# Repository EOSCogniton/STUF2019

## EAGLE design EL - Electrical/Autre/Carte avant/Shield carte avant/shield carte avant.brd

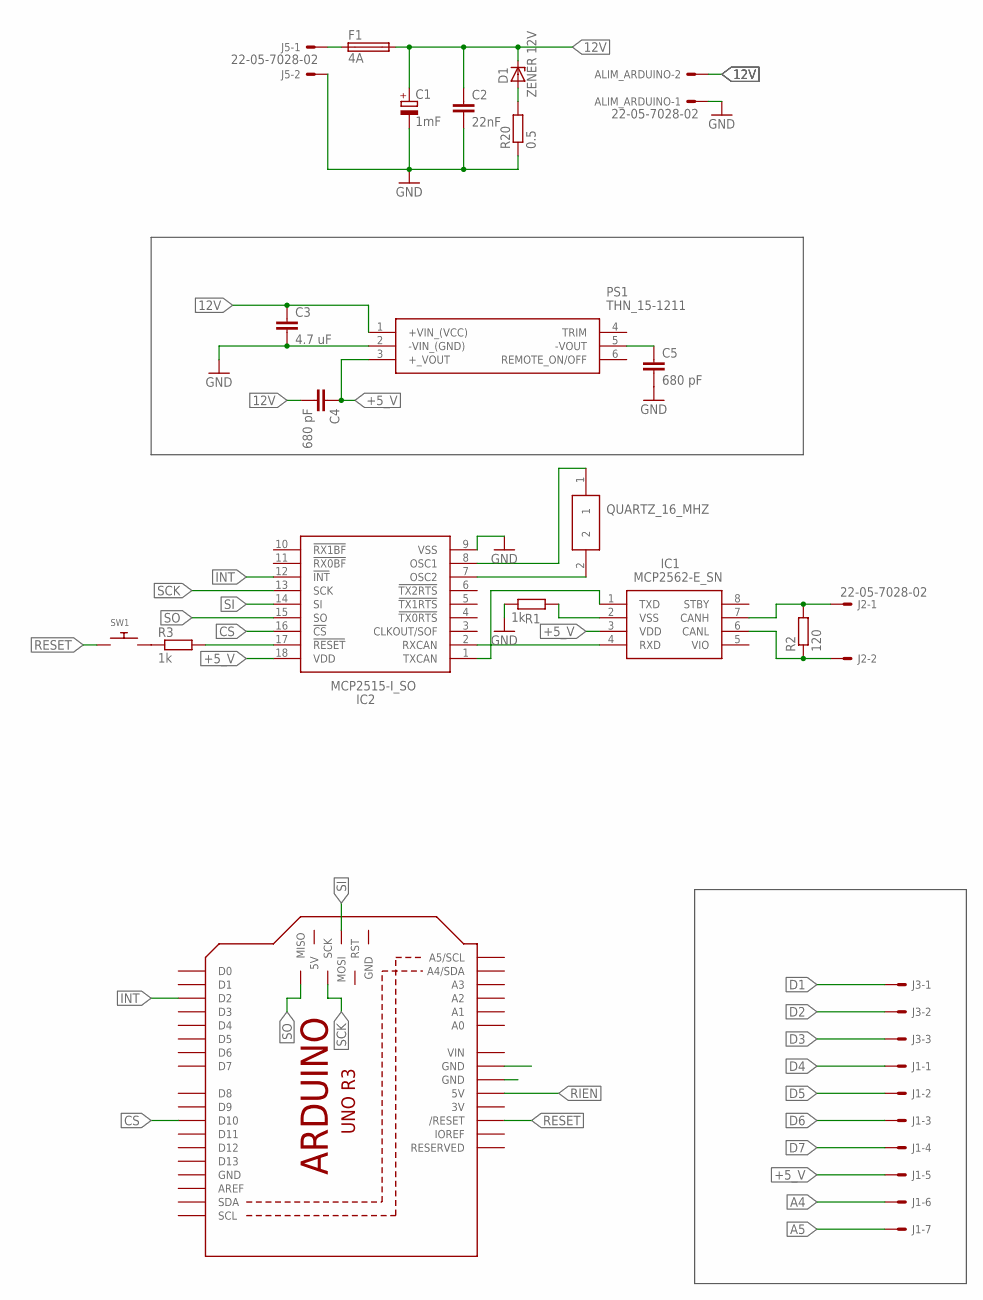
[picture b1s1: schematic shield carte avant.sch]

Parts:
ALIM_ARDUINO: 22-05-7028-02; 7395-02
C1: 1mF; E7,5-16
C2: 22nF; C025-025X050
C3: 4.7 uF; C025-024X044
C4, C5: 680 pF; C025-024X044
D1: ZENER 12V; DO41Z10
F1: 4A; SH25
IC1: MCP2562-E_SN; SOIC127P600X175-8N
IC2: MCP2515-I_SO; SOIC127P1030X265-18N
J1: 22-05-7078-07; 7395-07
J2, J5: 22-05-7028-02; 7395-02
J3: 22-05-7038-03; 7395-03
M1: ARDUINO_R3_ICSP; ARDUINOR3_ICSP
PS1: THN_15-1211; THN-15-SERIES
QUARTZ_16_MHZ: FOXSLF_160-20; HC49SLF_1
R1, R3: 1k; 0204/7
R2: 120; 0204/7
R20: 0.5; 0309/12
SW1: SWITCH_PUSHBUTTONEVQ-PE; TACT_PANA-EVQ

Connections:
3V: M1.3V
12V: ALIM_ARDUINO.2, C1.+, C2.1, C3.1, C4.2, D1.C, F1.2, PS1.1 (+VIN_(VCC))
+5_V: C4.1, IC1.3 (VDD), IC2.18 (VDD), J1.5, PS1.3 (+_VOUT)
A4: J1.6
A5: J1.7
CS: IC2.16 (!CS), M1.D10
D1: J3.1
D2: J3.2
D3: J3.3
D4: J1.1
D5: J1.2
D6: J1.3
D7: J1.4
GND: ALIM_ARDUINO.1, C1.-, C2.2, C3.2, C5.2, IC2.9 (VSS), J5.2, M1.GND, PS1.2 (-VIN_(GND)), R1.1, R20.1
INT: IC2.12 (!INT), M1.D2
unnamed: F1.1, J5.1
unnamed: C5.1, PS1.5 (-VOUT)
unnamed: D1.A, R20.2
unnamed: IC1.1 (TXD), IC2.1 (TXCAN)
unnamed: IC1.4 (RXD), IC2.2 (RXCAN)
unnamed: IC1.2 (VSS), R1.2
unnamed: IC1.7 (CANH), J2.1, R2.2
unnamed: IC1.6 (CANL), J2.2, R2.1
unnamed: IC2.7 (OSC2), QUARTZ_16_MHZ.2
unnamed: IC2.8 (OSC1), QUARTZ_16_MHZ.1
unnamed: R3.1, SW1.P$2
unnamed: IC2.17 (!RESET), R3.2
RESET: M1.RESET (/RESET), SW1.P$1
RIEN: M1.5V
SCK: IC2.13 (SCK), M1.SCK
SI: IC2.14 (SI), M1.MOSI
SO: IC2.15 (SO), M1.MISO
VIN: M1.VIN

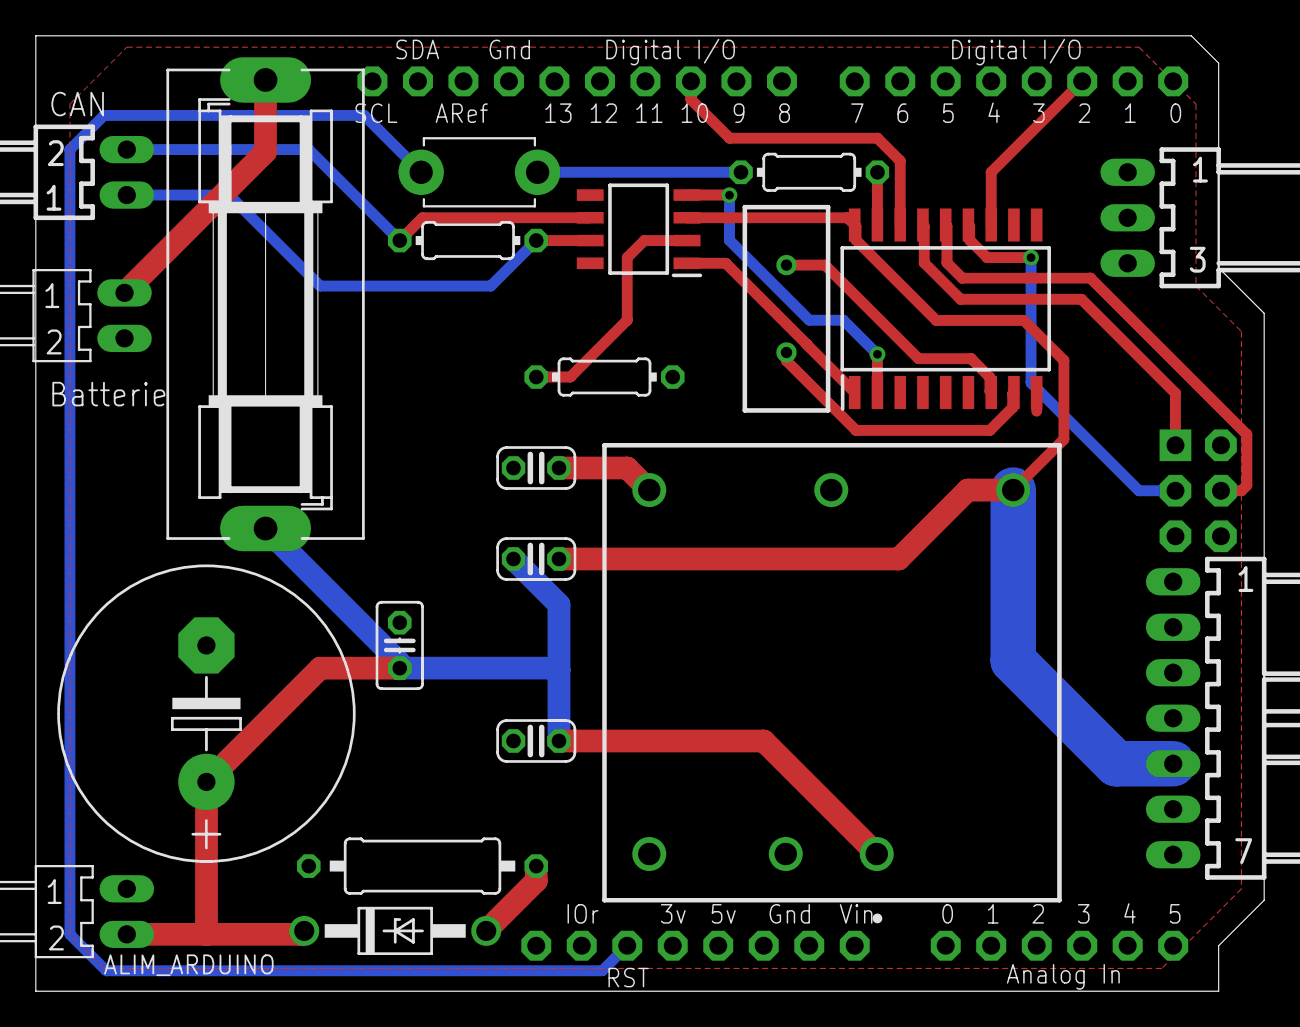
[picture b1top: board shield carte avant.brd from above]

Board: 2 copper layers, 68.6 x 53.3 mm, 22 parts (0 on the bottom side), 21 nets.

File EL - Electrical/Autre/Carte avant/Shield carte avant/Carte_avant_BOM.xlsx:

Qty | Value | Device | Description | Dispo au garage ? | Référence RS |  |  |  | oui
1 |  | SWITCH_PUSHBUTTONEVQ-PE | Buttons | Je sais pas |  |  |  |  | non
1 | 0.5 | R-EU_0309/12 | RESISTOR, European symbol | oui |  |  |  |  | Je sais pas
1 | 120 | R-EU_0204/7 | RESISTOR, European symbol | oui
2 | 1k | R-EU_0204/7 | RESISTOR, European symbol | oui
1 | 1mF | CPOL-EUE7.5-16 | POLARIZED CAPACITOR, European symbol | Je sais pas
2 |  | 22-05-7028-02 | CONNECTOR | oui
1 |  | 22-05-7028-02 | CONNECTOR | oui
1 |  | 22-05-7038-03 | CONNECTOR | Je sais pas
1 |  | 22-05-7078-07 | CONNECTOR | Je sais pas
1 | 22nF | C-EU025-025X050 | CAPACITOR, European symbol | Je sais pas
1 | 4.7 uF | C-EU025-024X044 | CAPACITOR, European symbol | Je sais pas
1 | 4A | SH25 | FUSE HOLDER grid 25 mm, OGN0031 8211, Schurter (Buerklin) | oui
2 | 680 pF | C-EU025-024X044 | CAPACITOR, European symbol | Je sais pas
1 |  | FOXSLF_160-20 | Crystal 16.000MHz HC49S HC-49-SLF Crystal 16MHz, ??30ppm, 2-Pin | Je sais pas
1 |  | MCP2515-I_SO | CAN Controller SPI data filtering SO18 | non
1 |  | MCP2562-E_SN | CAN Transceiver 1Mbps 5V 125degC SOIC8 CAN Transceiver 1MBps IEC 61000-4-2 Stan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 | non
1 |  | THN_15-1211 | TRACOPOWER Isolated DC-DC Converter, Vin 9 18 V dc, Vout 5V dc, I/O isolation 1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 | Je sais pas
1 | ZENER 12V | ZENER-DIODEDO41Z10 | Z-Diode | Je sais pas

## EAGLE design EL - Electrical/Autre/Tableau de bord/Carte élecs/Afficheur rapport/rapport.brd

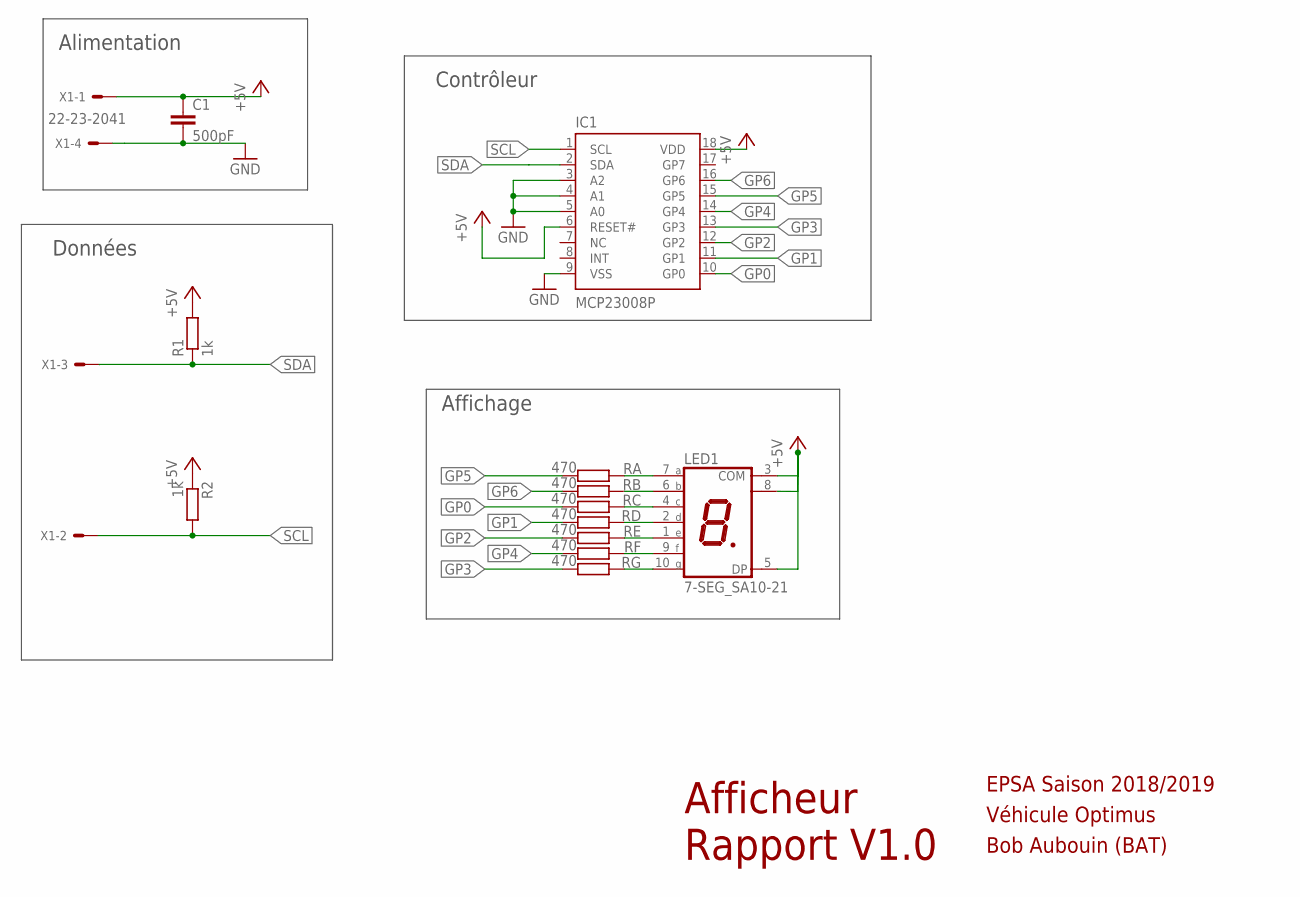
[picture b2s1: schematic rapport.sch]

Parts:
C1: 500pF; C025-025X050
IC1: MCP23008P; DIL18
LED1: 7-SEG_SA10-21; SA10-21
R1, R2: 1k; 0204/7
RA: 470; 0204/7
RB: 470; 0204/7
RC: 470; 0204/7
RD: 470; 0204/7
RE: 470; 0204/7
RF: 470; 0204/7
RG: 470; 0204/7
X1: 22-23-2041

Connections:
+5V: C1.1, IC1.6 (RESET#), IC1.18 (VDD), LED1.3 (COM), LED1.5 (DP), LED1.8 (COM), R1.2, R2.1, X1.1
GND: C1.2, IC1.3 (A2), IC1.4 (A1), IC1.5 (A0), IC1.9 (VSS), X1.4
GP0: IC1.10 (GP0), RC.2
GP1: IC1.11 (GP1), RD.2
GP2: IC1.12 (GP2), RE.2
GP3: IC1.13 (GP3), RG.2
GP4: IC1.14 (GP4), RF.2
GP5: IC1.15 (GP5), RA.2
GP6: IC1.16 (GP6), RB.2
unnamed: LED1.10 (G), RG.1
unnamed: LED1.9 (F), RF.1
unnamed: LED1.1 (E), RE.1
unnamed: LED1.2 (D), RD.1
unnamed: LED1.4 (C), RC.1
unnamed: LED1.6 (B), RB.1
unnamed: LED1.7 (A), RA.1
SCL: IC1.1 (SCL), R2.2, X1.2
SDA: IC1.2 (SDA), R1.1, X1.3

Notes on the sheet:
Afficheur Rapport V1.0
EPSA Saison 2018/2019
Alimentation
Contrôleur
Données
Affichage
Véhicule Optimus
Bob Aubouin (BAT)

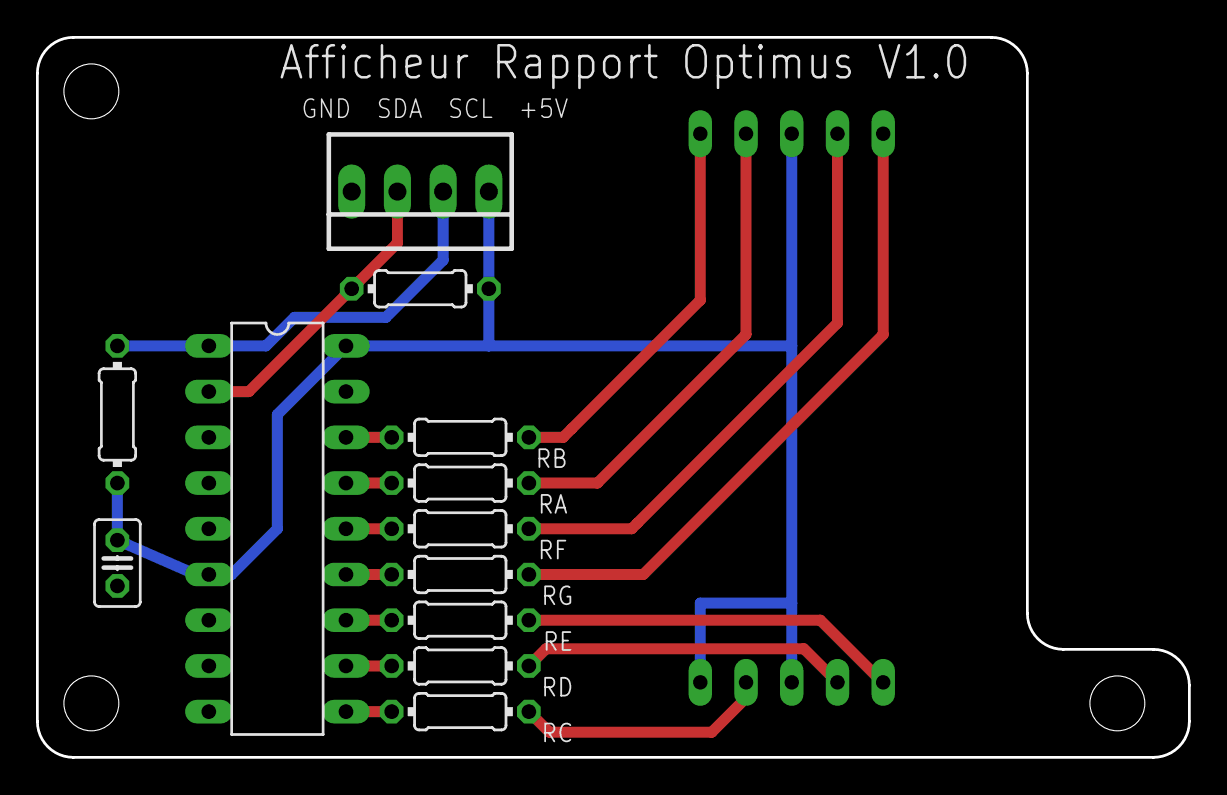
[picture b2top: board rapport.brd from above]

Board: 2 copper layers, 64.0 x 40.0 mm, 13 parts (1 on the bottom side), 18 nets.

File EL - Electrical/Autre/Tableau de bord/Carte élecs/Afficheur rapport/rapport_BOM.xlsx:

Qty | Value | Device | Description | Dispo au garage ? | Référence RS |  |  |  |  |  | oui
2 | 1k | R-EU_0204/7 | RESISTOR, European symbol | oui |  |  |  |  |  |  | non
1 |  | 22-23-2041 | .100 (2.54mm) Center Header - 4 Pin" | Je sais pas | 679-5596 |  |  |  |  |  | Je sais pas
7 | 470 | R-EU_0204/7 | RESISTOR, European symbol | oui
1 | 500pF | C-EU025-025X050 | CAPACITOR, European symbol | Je sais pas | 831-3026
1 |  | 7-SEG_SA10-21 | Kingbright 14.2mm (0.56 INCH) SINGLE DIGIT NUMERIC DUISPLAY | oui
1 |  | MCP23008P | 8-Bit I/O Expander with I2C Interface | oui

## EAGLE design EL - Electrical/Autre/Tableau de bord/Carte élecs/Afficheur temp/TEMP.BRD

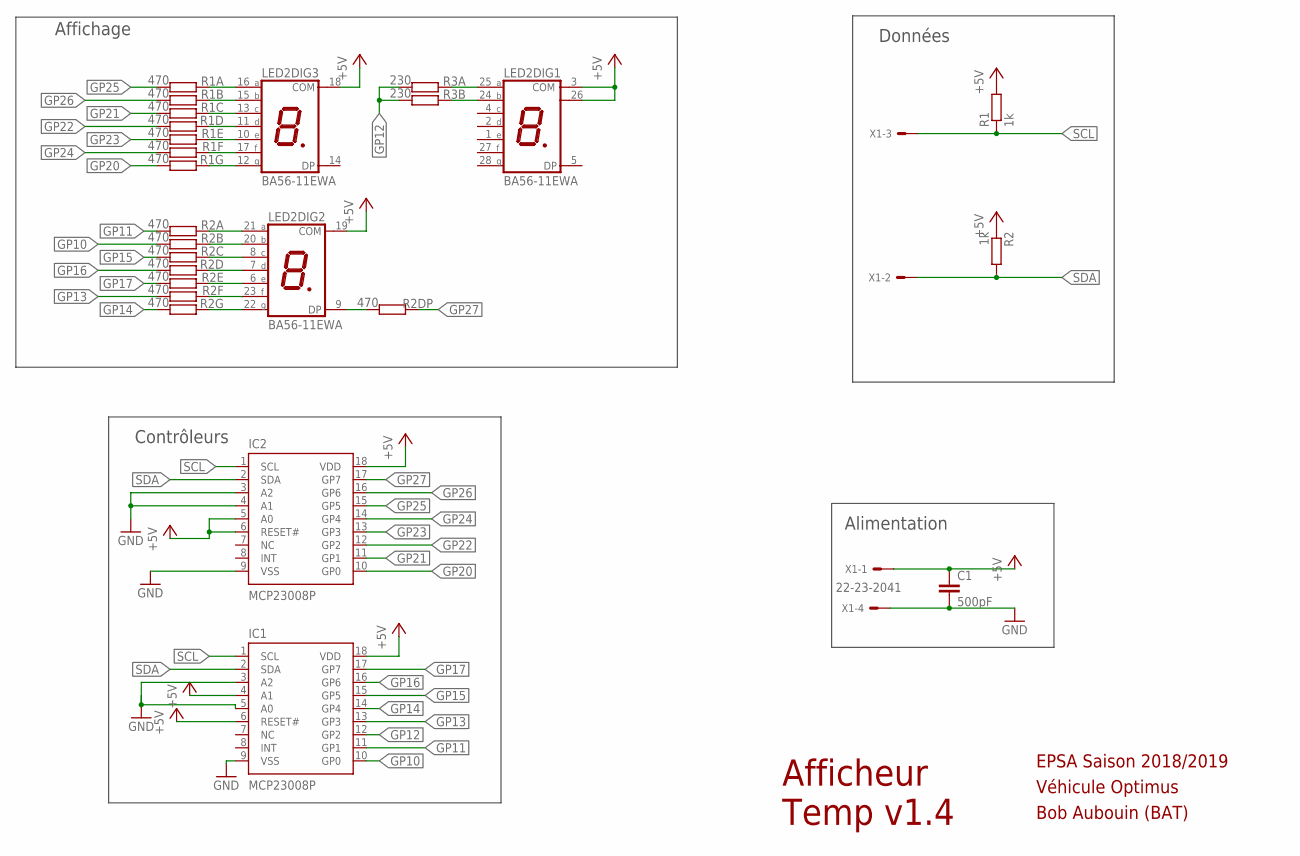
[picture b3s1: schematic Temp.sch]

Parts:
C1: 500pF; C025-025X050
IC1, IC2: MCP23008P; DIL18
LED2: BA56-11EWA; BA/BC56
R1, R2: 1k; 0204/7
R1A, R1B, R1C, R1D, R1E, R1F, R1G, R2A, R2B, R2C, R2D, R2DP, R2E, R2F, R2G: 470; 0204/7
R3A, R3B: 230; 0204/7
X1: 22-23-2041

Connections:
+5V: C1.1, IC1.4 (A1), IC1.6 (RESET#), IC1.18 (VDD), IC2.5 (A0), IC2.6 (RESET#), IC2.18 (VDD), LED2.3 (COM), LED2.18 (COM), LED2.19 (COM), LED2.26 (COM), R1.2, R2.1, X1.1
GND: C1.2, IC1.3 (A2), IC1.5 (A0), IC1.9 (VSS), IC2.3 (A2), IC2.4 (A1), IC2.9 (VSS), X1.4
GP10: IC1.10 (GP0), R2B.2
GP11: IC1.11 (GP1), R2A.2
GP12: IC1.12 (GP2), R3A.2, R3B.2
GP13: IC1.13 (GP3), R2F.2
GP14: IC1.14 (GP4), R2G.2
GP15: IC1.15 (GP5), R2C.2
GP16: IC1.16 (GP6), R2D.2
GP17: IC1.17 (GP7), R2E.2
GP20: IC2.10 (GP0), R1G.2
GP21: IC2.11 (GP1), R1C.2
GP22: IC2.12 (GP2), R1D.2
GP23: IC2.13 (GP3), R1E.2
GP24: IC2.14 (GP4), R1F.2
GP25: IC2.15 (GP5), R1A.2
GP26: IC2.16 (GP6), R1B.2
GP27: IC2.17 (GP7), R2DP.1
unnamed: LED2.16 (A), R1A.1
unnamed: LED2.15 (B), R1B.1
unnamed: LED2.13 (C), R1C.1
unnamed: LED2.11 (D), R1D.1
unnamed: LED2.10 (E), R1E.1
unnamed: LED2.17 (F), R1F.1
unnamed: LED2.12 (G), R1G.1
unnamed: LED2.21 (A), R2A.1
unnamed: LED2.20 (B), R2B.1
unnamed: LED2.8 (C), R2C.1
unnamed: LED2.7 (D), R2D.1
unnamed: LED2.6 (E), R2E.1
unnamed: LED2.23 (F), R2F.1
unnamed: LED2.22 (G), R2G.1
unnamed: LED2.9 (DP), R2DP.2
unnamed: LED2.24 (B), R3B.1
unnamed: LED2.25 (A), R3A.1
SCL: IC1.1 (SCL), IC2.1 (SCL), R1.1, X1.3
SDA: IC1.2 (SDA), IC2.2 (SDA), R2.2, X1.2

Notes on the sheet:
Afficheur Temp v1.4
EPSA Saison 2018/2019
Alimentation
Contrôleurs
Données
Affichage
Véhicule Optimus
Bob Aubouin (BAT)

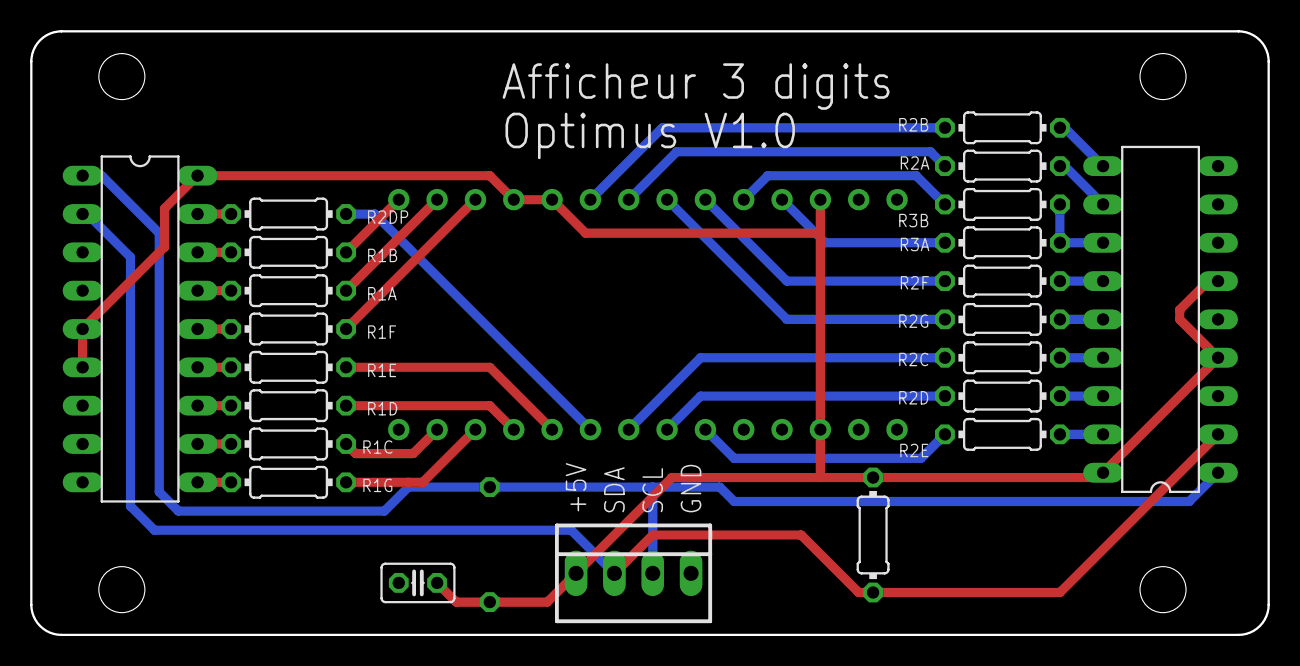
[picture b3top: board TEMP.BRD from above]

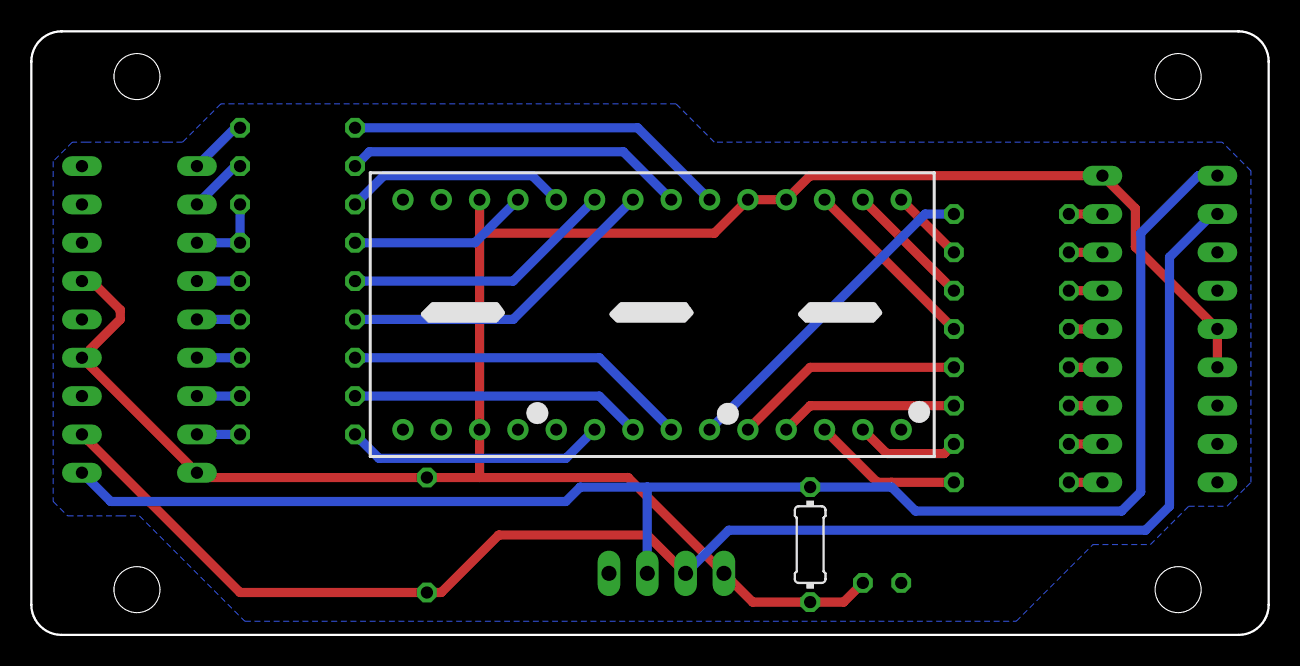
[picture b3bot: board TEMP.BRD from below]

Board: 2 copper layers, 82.0 x 40.0 mm, 24 parts (2 on the bottom side), 37 nets.

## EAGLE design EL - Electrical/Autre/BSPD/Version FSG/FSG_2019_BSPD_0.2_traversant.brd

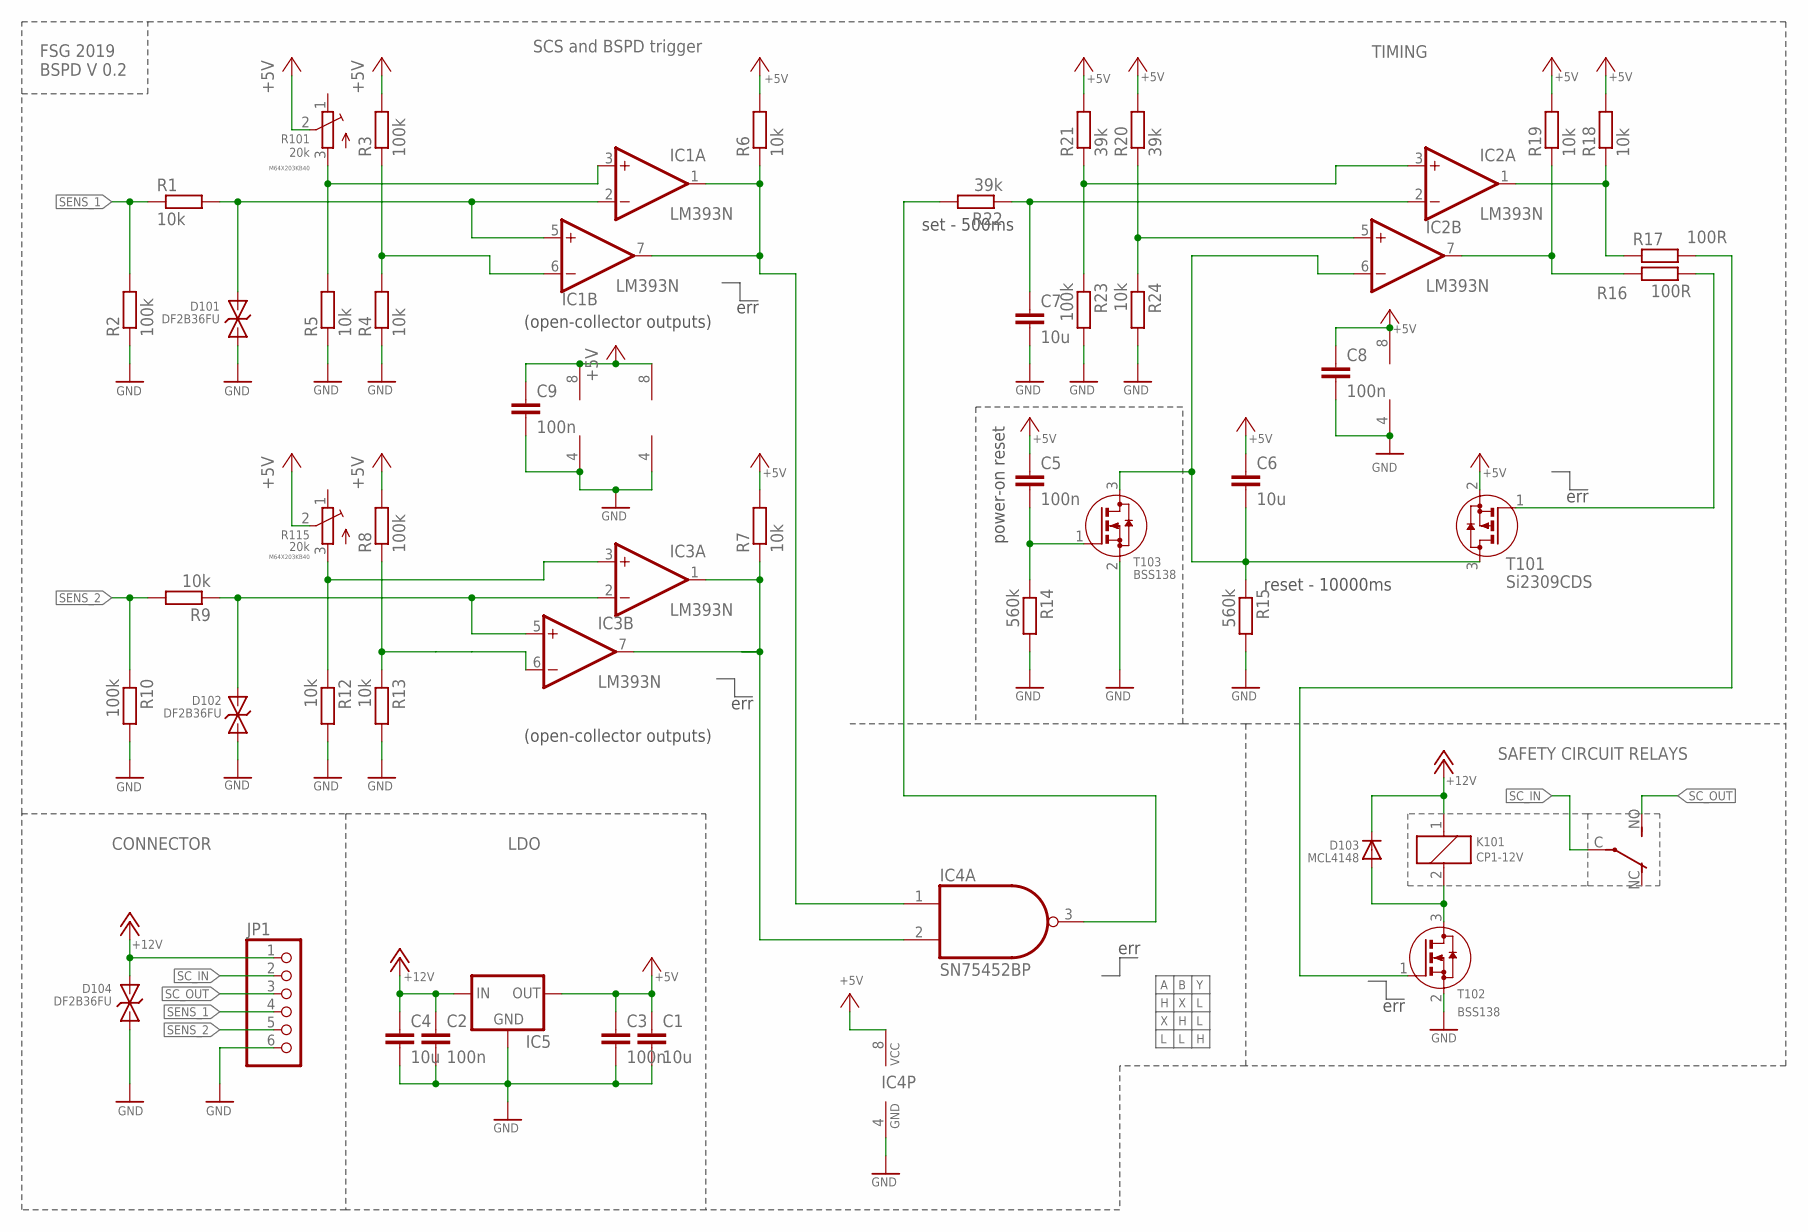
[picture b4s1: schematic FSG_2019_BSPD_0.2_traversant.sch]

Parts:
C1, C4, C6, C7: 10u; C075-052X106
C2, C3, C5, C8, C9: 100n; C025-024X044
D101, D102, D104: DF2B36FU; SOD323
D103: MCL4148; MICROMELF
IC1, IC2, IC3: LM393N; DIL08
IC4: SN75452BP; DIL08
IC5: LM1117V; 78XXS
JP1: PINHD-1X6; 1X06
K101: CP1-12V; CP1
R1, R4, R5, R6, R7, R9, R12, R13, R18, R19, R24: 10k; 0204/7
R2, R3, R8, R10, R23: 100k; 0204/7
R14, R15: 560k; 0204/7
R16, R17: 100R; 0204/7
R20, R21, R22: 39k; 0204/7
R101, R115: 20k; M64X201KB40
T101: Si2309CDS; SOT-23
T102, T103: BSS138; SOT-23

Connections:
+5V: C1.1, C3.1, C5.1, C6.1, C8.1, C9.1, IC1.8 (V+), IC2.8 (V+), IC3.8 (V+), IC4.8 (VCC), IC5.OUT, R3.2, R6.2, R7.2, R8.2, R18.2, R19.2, R20.2, R21.2, R101.2 (M), R115.2 (M), T101.2 (S)
+12V: C2.1, C4.1, D103.C, D104.2 (C), IC5.IN, JP1.1, K101.1
BRAKE_F: D101.2 (C), IC1.2 (-IN), IC1.5 (+IN), R1.2
DF: D102.2 (C), IC3.2 (-IN), IC3.5 (+IN), R9.1
GND: C1.2, C2.2, C3.2, C4.2, C7.2, C8.2, C9.2, D101.1 (A), D102.1 (A), D104.1 (A), IC1.4 (V-), IC2.4 (V-), IC3.4 (V-), IC4.4 (GND), IC5.GND, JP1.6, R2.1, R4.1, R5.1, R10.2, R12.2, R13.2, R14.2, R15.2, R23.2, R24.2, T102.2 (S), T103.2 (S)
unnamed: IC2.5 (+IN), R20.1, R24.1
unnamed: IC3.1 (OUT), IC3.7 (OUT), IC4.2 (I1), R7.1
unnamed: IC4.3 (O), R22.2
unnamed: IC2.7 (OUT), R16.1, R19.1
unnamed: C5.2, R14.1, T103.1 (G)
unnamed: IC1.3 (+IN), R5.2, R101.3 (A)
unnamed: C6.2, IC2.6 (-IN), R15.1, T101.3 (D), T103.3 (D)
unnamed: IC1.1 (OUT), IC1.7 (OUT), IC4.1 (I0), R6.1
unnamed: R17.2, T102.1 (G)
unnamed: D103.A, K101.2, T102.3 (D)
unnamed: IC3.3 (+IN), R12.1, R115.3 (A)
unnamed: IC2.3 (+IN), R21.1, R23.1
unnamed: IC1.6 (-IN), R3.1, R4.2
unnamed: IC2.1 (OUT), R17.1, R18.1
unnamed: IC3.6 (-IN), R8.1, R13.1
unnamed: C7.1, IC2.2 (-IN), R22.1
unnamed: R16.2, T101.1 (G)
SC_IN: JP1.2, K101.C
SC_OUT: JP1.3, K101.NO (S)
SENS_1: JP1.4, R1.1, R2.2
SENS_2: JP1.5, R9.2, R10.1

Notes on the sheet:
M64X203KB40
FSG 2019 BSPD V 0.2
CONNECTOR
LDO
SAFETY CIRCUIT RELAYS
err
TIMING
SCS and BSPD trigger
power-on reset
set - 500ms
reset - 10000ms
(open-collector outputs)

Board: 2 copper layers, 48 parts (0 on the bottom side), 26 nets, no tracks yet.

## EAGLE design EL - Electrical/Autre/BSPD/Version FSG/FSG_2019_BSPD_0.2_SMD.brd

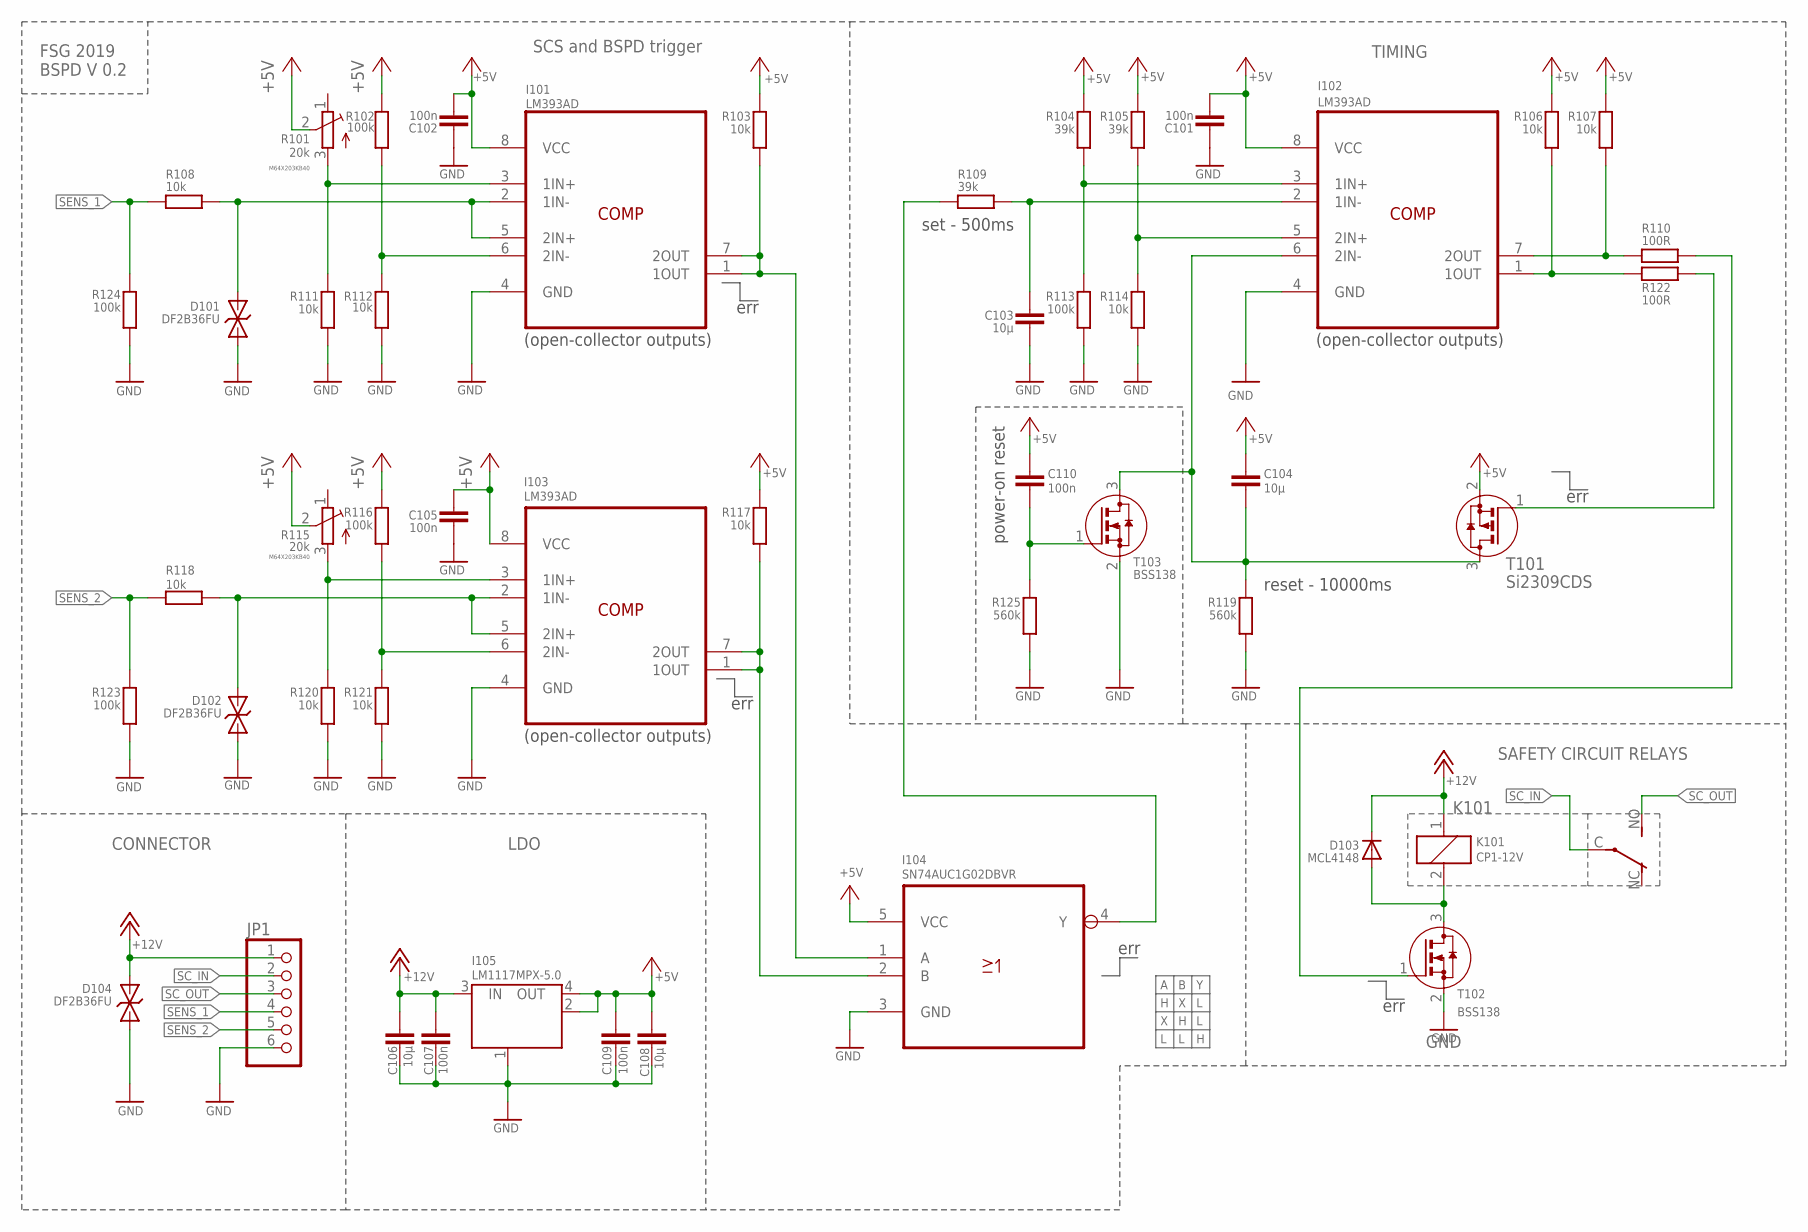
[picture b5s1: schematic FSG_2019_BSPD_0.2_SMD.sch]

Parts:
C101, C102, C105, C107, C109, C110: 100n; C0603
C103, C106, C108: 10µ; C1206
C104: 10µ; C1206K
D101, D102, D104: DF2B36FU; SOD323
D103: MCL4148; MICROMELF
I101, I102, I103: LM393AD; SOIC127P600X175-8N
I104: SN74AUC1G02DBVR; SOT95P280X145-5N
I105: LM1117MPX-5.0; LINEAR_SOT223
JP1: PINHD-1X6; 1X06
K101: CP1-12V; CP1
R101, R115: 20k; M64X201KB40
R102, R113, R116, R123, R124: 100k; R0603
R103, R106, R107, R108, R111, R112, R114, R117, R118, R120, R121: 10k; R0603
R104, R105, R109: 39k; R0603
R110, R122: 100R; R0603
R119, R125: 560k; R0603
T101: Si2309CDS; SOT-23
T102, T103: BSS138; SOT-23

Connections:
+5V: C101.2, C102.2, C104.1, C105.2, C108.1, C109.2, C110.1, I101.8 (VCC), I102.8 (VCC), I103.8 (VCC), I104.5 (VCC), I105.2 (OUT), I105.4 (OUT), R101.2 (M), R102.1, R103.1, R104.2, R105.2, R106.2, R107.2, R115.2 (M), R116.1, R117.1, T101.2 (S)
+12V: C106.1, C107.1, D103.C, D104.2 (C), I105.3 (IN), JP1.1, K101.1
BRAKE_F: D101.2 (C), I101.2 (1IN-), I101.5 (2IN+), R108.2
DF: D102.2 (C), I103.2 (1IN-), I103.5 (2IN+), R118.2
GND: C101.1, C102.1, C103.2, C105.1, C106.2, C107.2, C108.2, C109.1, D101.1 (A), D102.1 (A), D104.1 (A), I101.4 (GND), I102.4 (GND), I103.4 (GND), I104.3 (GND), I105.1 (GND/ADJ), JP1.6, R111.2, R112.2, R113.1, R114.1, R119.1, R120.2, R121.2, R123.1, R124.1, R125.1, T102.2 (S), T103.2 (S)
unnamed: I102.5 (2IN+), R105.1, R114.2
unnamed: I103.1 (1OUT), I103.7 (2OUT), I104.2 (B), R117.2
unnamed: I101.1 (1OUT), I101.7 (2OUT), I104.1 (A), R103.2
unnamed: I102.1 (1OUT), R106.1, R122.2
unnamed: C110.2, R125.2, T103.1 (G)
unnamed: I101.3 (1IN+), R101.3 (A), R111.1
unnamed: C104.2, I102.6 (2IN-), R119.2, T101.3 (D), T103.3 (D)
unnamed: I103.3 (1IN+), R115.3 (A), R120.1
unnamed: R110.1, T102.1 (G)
unnamed: D103.A, K101.2, T102.3 (D)
unnamed: C103.1, I102.2 (1IN-), R109.1
unnamed: I102.3 (1IN+), R104.1, R113.2
unnamed: I101.6 (2IN-), R102.2, R112.1
unnamed: I102.7 (2OUT), R107.1, R110.2
unnamed: I103.6 (2IN-), R116.2, R121.1
unnamed: R122.1, T101.1 (G)
unnamed: I104.4 (Y), R109.2
SC_IN: JP1.2, K101.C
SC_OUT: JP1.3, K101.NO (S)
SENS_1: JP1.4, R108.1, R124.2
SENS_2: JP1.5, R118.1, R123.2

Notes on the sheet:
COMP
M64X203KB40
FSG 2019 BSPD V 0.2
CONNECTOR
LDO
SAFETY CIRCUIT RELAYS
err
TIMING
SCS and BSPD trigger
power-on reset
set - 500ms
reset - 10000ms
(open-collector outputs)

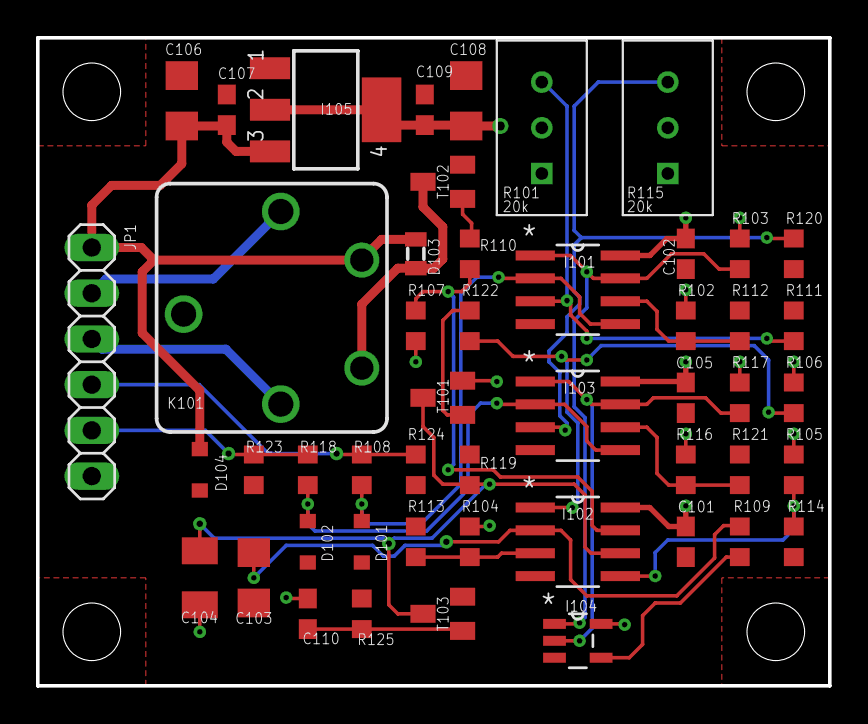
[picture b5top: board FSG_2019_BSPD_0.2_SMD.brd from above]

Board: 2 copper layers, 44.0 x 36.0 mm, 49 parts (0 on the bottom side), 26 nets.

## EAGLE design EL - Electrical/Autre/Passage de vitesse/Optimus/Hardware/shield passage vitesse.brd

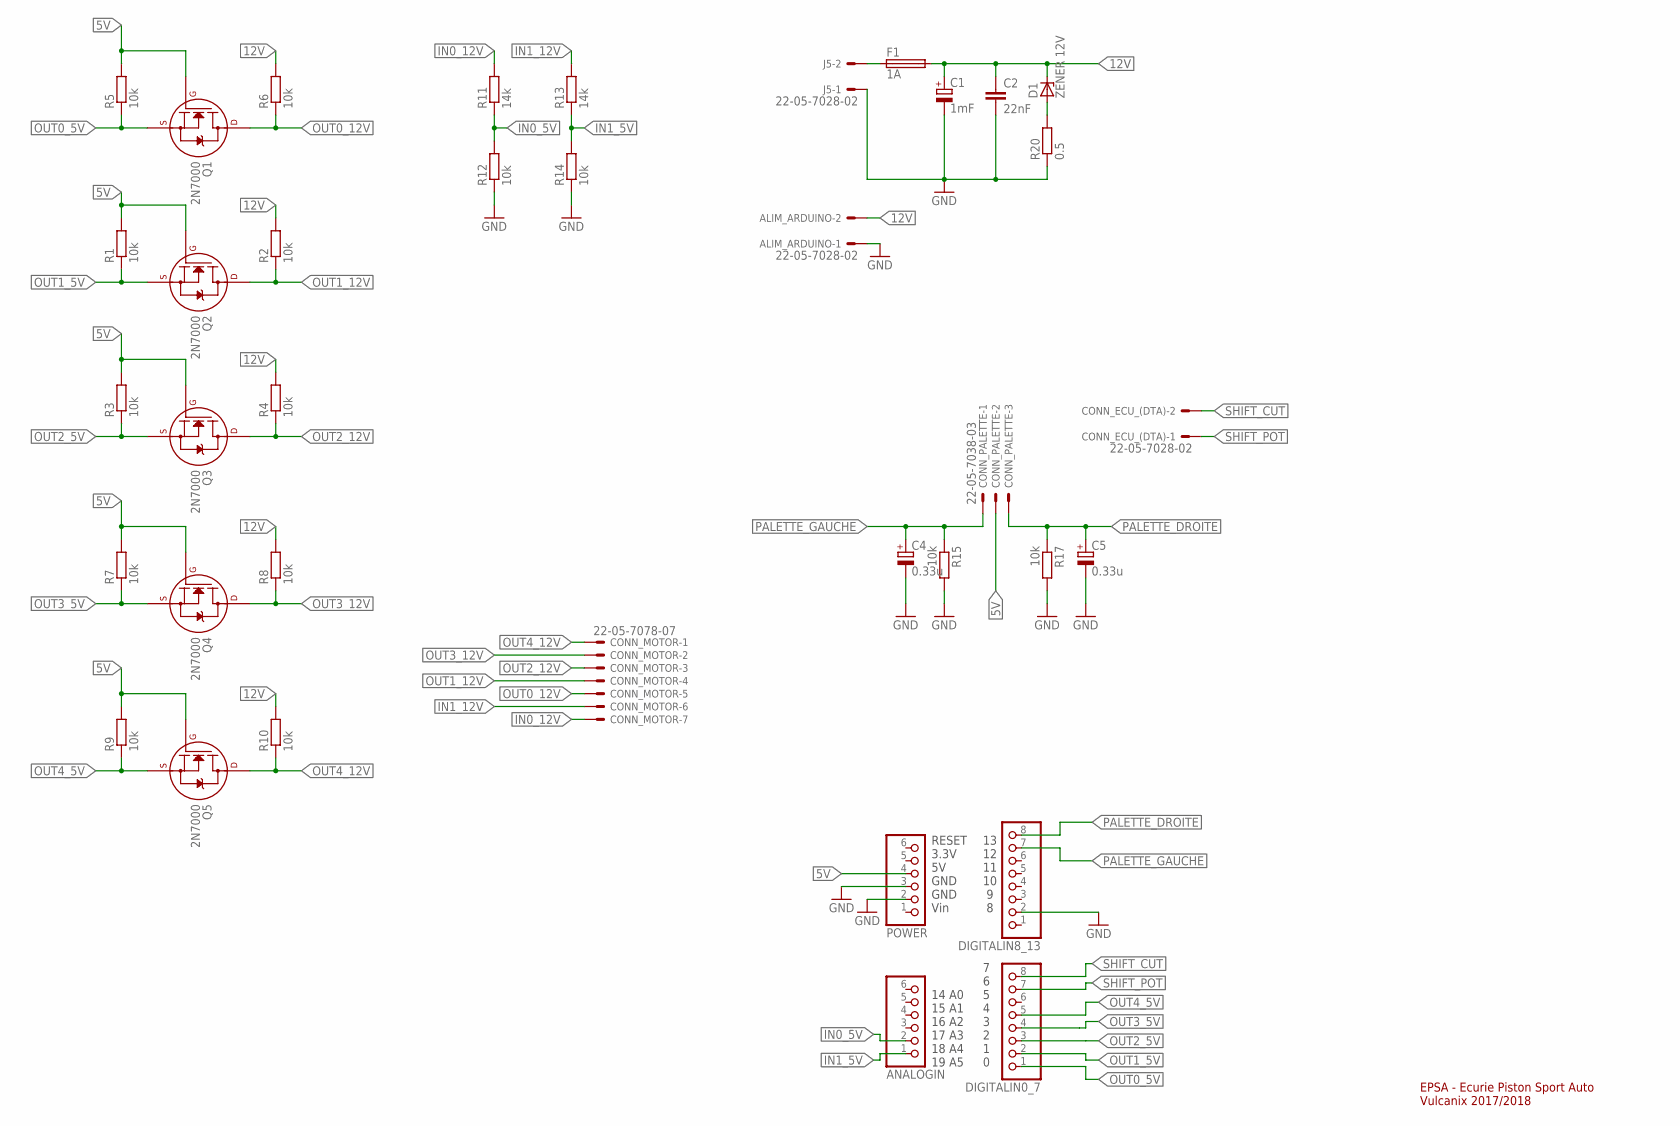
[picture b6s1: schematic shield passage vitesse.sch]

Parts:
ALIM_ARDUINO: 22-05-7028-02; 7395-02
ANALOGIN: PINHD-1X6CB; 1X06-CLEANBIG
C1: 1mF; E7,5-16
C2: 22nF; C025-025X050
C4, C5: 0.33u; E2,5-6E
CONN_ECU_(DTA): 22-05-7028-02; 7395-02
CONN_MOTOR: 22-05-7078-07; 7395-07
CONN_PALETTE: 22-05-7038-03; 7395-03
D1: ZENER 12V; DO41Z10
DIGITALIN0_7, DIGITALIN8_13: PINHD-1X8CLEANBIG; 1X08-CLEANBIG
F1: 1A; SH25
J5: 22-05-7028-02; 7395-02
POWER: PINHD-1X6CB; 1X06-CLEANBIG
Q1, Q2, Q3, Q4, Q5: 2N7000; TO-92
R1, R2, R3, R4, R5, R6, R7, R8, R9, R10, R12, R14, R15, R17: 10k; 0204/7
R11, R13: 14k; 0204/7
R20: 0.5; 0309/12

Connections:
5V: CONN_PALETTE.2, POWER.4, Q1.2 (G), Q2.2 (G), Q3.2 (G), Q4.2 (G), Q5.2 (G), R1.2, R3.2, R5.2, R7.2, R9.2
12V: ALIM_ARDUINO.2, C1.+, C2.1, D1.C, F1.2, R2.2, R4.2, R6.2, R8.2, R10.2
GND: ALIM_ARDUINO.1, C1.-, C2.2, C4.-, C5.-, DIGITALIN8_13.2, J5.1, POWER.2, POWER.3, R12.1, R14.1, R15.2, R17.2, R20.1
IN0_5V: ANALOGIN.2, R11.1, R12.2
IN0_12V: CONN_MOTOR.7, R11.2
IN1_5V: ANALOGIN.1, R13.1, R14.2
IN1_12V: CONN_MOTOR.6, R13.2
unnamed: F1.1, J5.2
unnamed: D1.A, R20.2
OUT0_5V: DIGITALIN0_7.1, Q1.1 (S), R5.1
OUT0_12V: CONN_MOTOR.5, Q1.3 (D), R6.1
OUT1_5V: DIGITALIN0_7.2, Q2.1 (S), R1.1
OUT1_12V: CONN_MOTOR.4, Q2.3 (D), R2.1
OUT2_5V: DIGITALIN0_7.3, Q3.1 (S), R3.1
OUT2_12V: CONN_MOTOR.3, Q3.3 (D), R4.1
OUT3_5V: DIGITALIN0_7.4, Q4.1 (S), R7.1
OUT3_12V: CONN_MOTOR.2, Q4.3 (D), R8.1
OUT4_5V: DIGITALIN0_7.5, Q5.1 (S), R9.1
OUT4_12V: CONN_MOTOR.1, Q5.3 (D), R10.1
PALETTE_DROITE: C5.+, CONN_PALETTE.3, DIGITALIN8_13.8, R17.1
PALETTE_GAUCHE: C4.+, CONN_PALETTE.1, DIGITALIN8_13.7, R15.1
SHIFT_CUT: CONN_ECU_(DTA).2, DIGITALIN0_7.8
SHIFT_POT: CONN_ECU_(DTA).1, DIGITALIN0_7.7

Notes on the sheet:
EPSA - Ecurie Piston Sport Auto Vulcanix 2017/2018
7 6 5 4 3 2 1 0
13 12 11 10 9 8
14 A0 15 A1 16 A2 17 A3 18 A4 19 A5
RESET 3.3V 5V GND GND Vin

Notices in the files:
parts and their libraries:
wurth_elektronik_passive_rev16d: Copyright: Würth Elektronik
microbuilder: This work is placed in the public domain, and may be freely used for commercial and non-commercial work with the following conditions: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
